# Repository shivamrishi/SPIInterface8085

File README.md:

# SPIInterface8085

Protocols like SPI and I2C are not supported by 8085 processors without any external peripherals and IC's. 
Therefore, bit-banging is used to communicate with 8085 based system. Addressable latches are used for this purpose. the details can be found in compass.sch.

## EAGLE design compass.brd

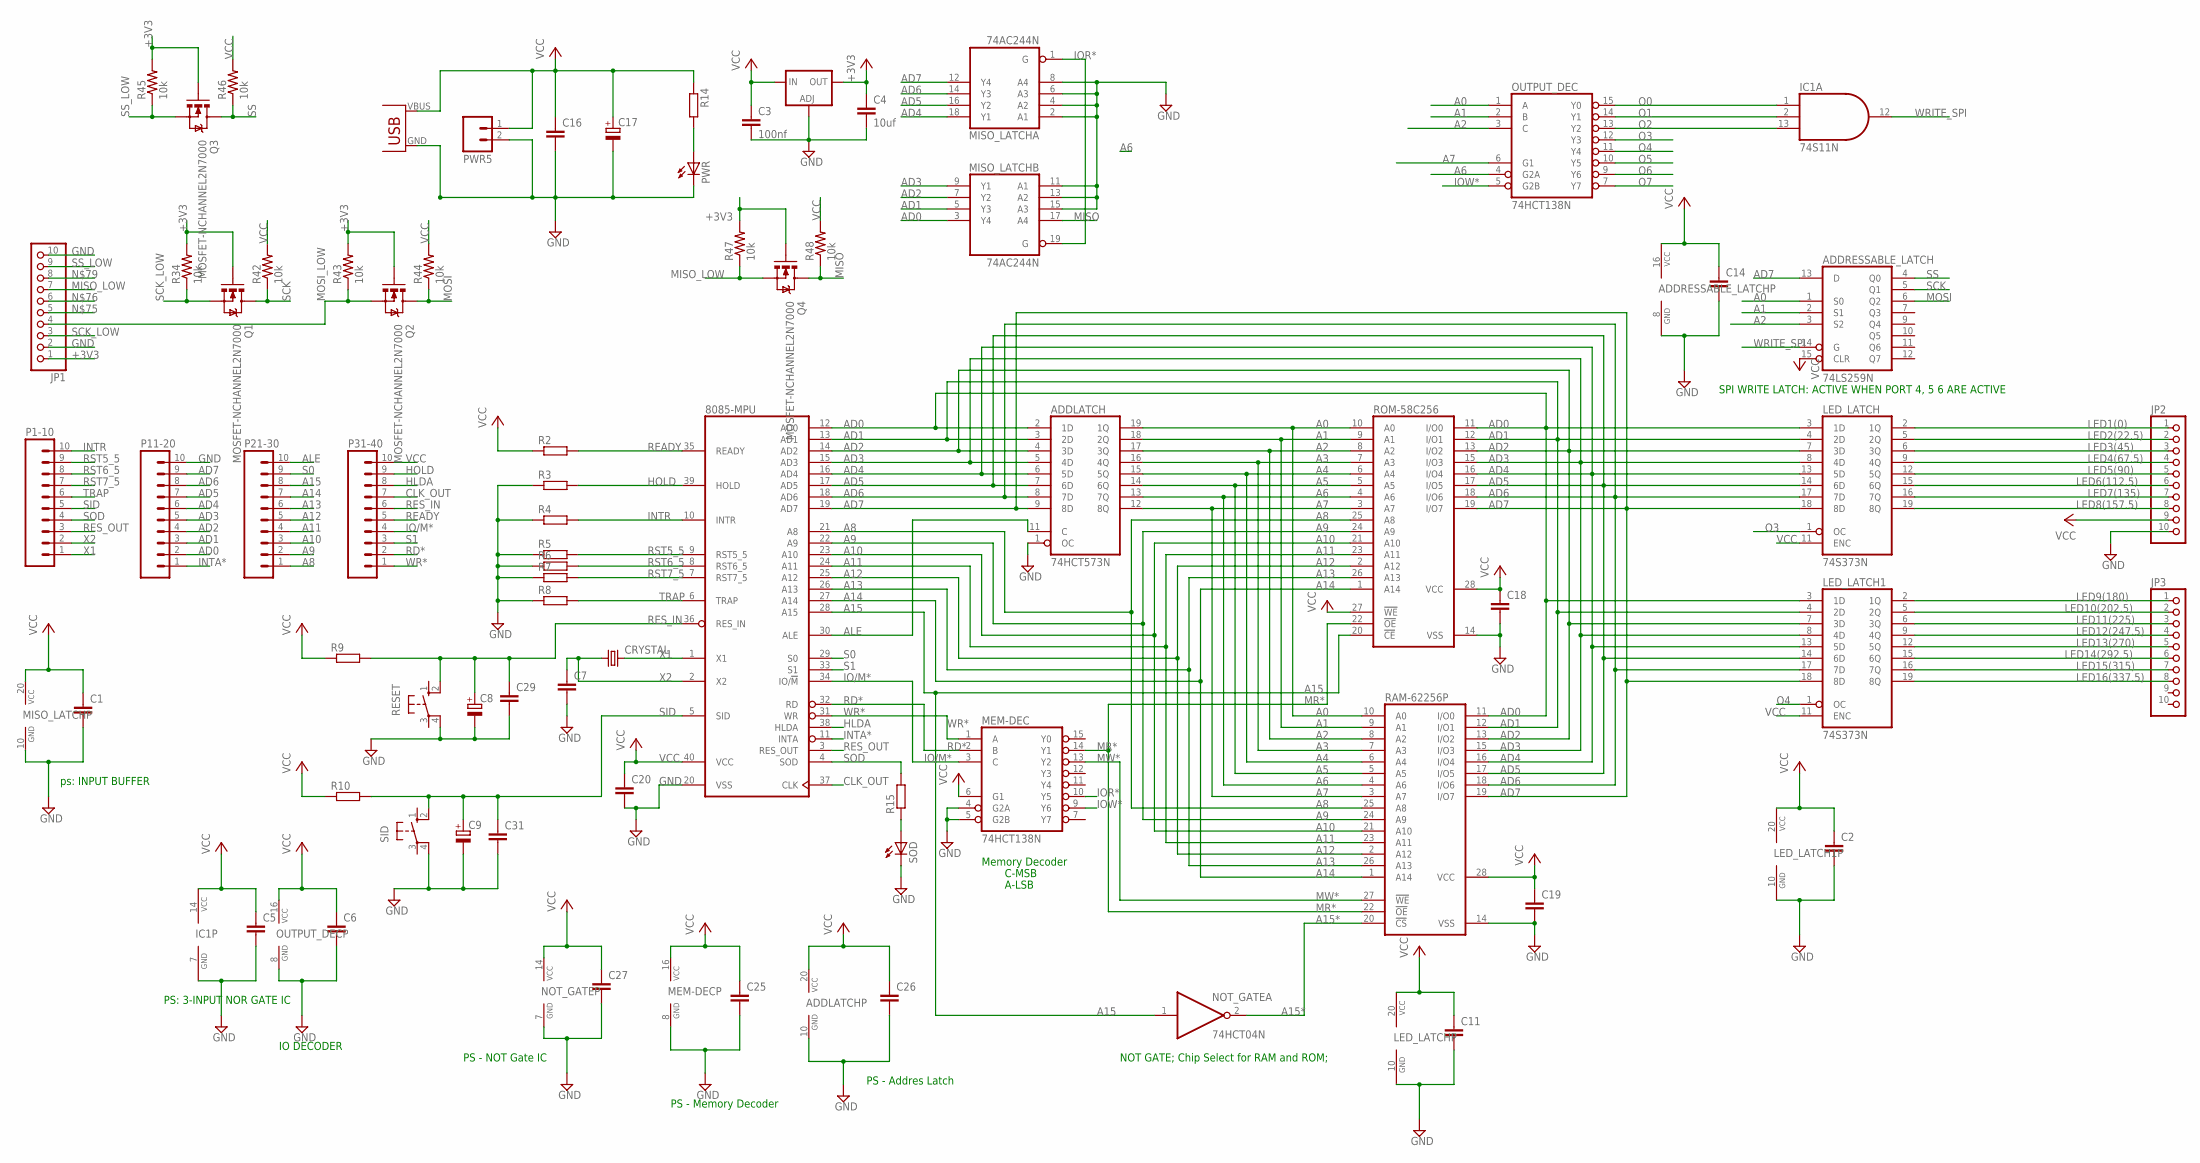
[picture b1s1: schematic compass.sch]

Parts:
8085-MPU: 8085; DIL40
ADDLATCH: 74HCT573N; DIL20
ADDRESSABLE_LATCH: 74LS259N; DIL16
C1, C2, C5, C6, C7, C11, C14, C16, C18, C19, C20, C25, C26, C27, C29, C31: C-EU025-025X050; C025-025X050
C3: 100nf; C025-025X050
C4: 10uf; C025-025X050
C8, C9, C17: CPOL-EUE2.5-6; E2,5-6
CRYSTAL: CRYSTALHC49US; HC49US
IC1: 74S11N; DIL14
IC10: LD117AS33TR; SOT223
JP1, JP2, JP3: PINHD-1X10; 1X10
LED_LATCH, LED_LATCH1: 74S373N; DIL20
MEM-DEC: 74HCT138N; DIL16
MISO_LATCH: 74AC244N; DIL20
NOT_GATE: 74HCT04N; DIL14
OUTPUT_DEC: 74HCT138N; DIL16
P1-10, P11-20, P21-30, P31-40: M10; 10P
PWR: LED5MM
PWR5: M02; 02P
Q1, Q2, Q3, Q4: MOSFET-NCHANNEL2N7000; TO-92
R2, R3, R4, R5, R6, R7, R8, R9, R10, R14, R15: R-EU_0204/7; 0204/7
R34, R42, R43, R44, R45, R46, R47, R48: 10k; 0204/7
RAM-62256P: 62256P; DIL28-6
RESET: 10-XX; B3F-10XX
ROM-58C256: 58C256P; DIL28-6
SID: 10-XX; B3F-10XX
SOD: LED5MM
USB: USB(POWER)

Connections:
+3V3: C4.1, IC10.4 (OUT), JP1.1, Q1.2 (G), Q2.2 (G), Q3.2 (G), Q4.2 (G), R34.2, R43.2, R45.2, R47.2
A0: ADDLATCH.19 (1Q), ADDRESSABLE_LATCH.1 (S0), OUTPUT_DEC.1 (A), RAM-62256P.10 (A0), ROM-58C256.10 (A0)
A1: ADDLATCH.18 (2Q), ADDRESSABLE_LATCH.2 (S1), OUTPUT_DEC.2 (B), RAM-62256P.9 (A1), ROM-58C256.9 (A1)
A2: ADDLATCH.17 (3Q), ADDRESSABLE_LATCH.3 (S2), OUTPUT_DEC.3 (C), RAM-62256P.8 (A2), ROM-58C256.8 (A2)
A3: ADDLATCH.16 (4Q), RAM-62256P.7 (A3), ROM-58C256.7 (A3)
A4: ADDLATCH.15 (5Q), RAM-62256P.6 (A4), ROM-58C256.6 (A4)
A5: ADDLATCH.14 (6Q), RAM-62256P.5 (A5), ROM-58C256.5 (A5)
A6: ADDLATCH.13 (7Q), OUTPUT_DEC.4 (G2A), RAM-62256P.4 (A6), ROM-58C256.4 (A6)
A7: ADDLATCH.12 (8Q), OUTPUT_DEC.6 (G1), RAM-62256P.3 (A7), ROM-58C256.3 (A7)
A8: 8085-MPU.21 (A8), P21-30.1, RAM-62256P.25 (A8), ROM-58C256.25 (A8)
A9: 8085-MPU.22 (A9), P21-30.2, RAM-62256P.24 (A9), ROM-58C256.24 (A9)
A10: 8085-MPU.23 (A10), P21-30.3, RAM-62256P.21 (A10), ROM-58C256.21 (A10)
A11: 8085-MPU.24 (A11), P21-30.4, RAM-62256P.23 (A11), ROM-58C256.23 (A11)
A12: 8085-MPU.25 (A12), P21-30.5, RAM-62256P.2 (A12), ROM-58C256.2 (A12)
A13: 8085-MPU.26 (A13), P21-30.6, RAM-62256P.26 (A13), ROM-58C256.26 (A13)
A14: 8085-MPU.27 (A14), P21-30.7, RAM-62256P.1 (A14), ROM-58C256.1 (A14)
A15: 8085-MPU.28 (A15), NOT_GATE.1 (I), P21-30.8, ROM-58C256.20 (!CE)
A15*: NOT_GATE.2 (O), RAM-62256P.20 (!CS)
AD0: 8085-MPU.12 (AD0), ADDLATCH.2 (1D), LED_LATCH.3 (1D), LED_LATCH1.3 (1D), MISO_LATCH.3 (Y4), P11-20.2, RAM-62256P.11 (I/O0), ROM-58C256.11 (I/O0)
AD1: 8085-MPU.13 (AD1), ADDLATCH.3 (2D), LED_LATCH.4 (2D), LED_LATCH1.4 (2D), MISO_LATCH.5 (Y3), P11-20.3, RAM-62256P.12 (I/O1), ROM-58C256.12 (I/O1)
AD2: 8085-MPU.14 (AD2), ADDLATCH.4 (3D), LED_LATCH.7 (3D), LED_LATCH1.7 (3D), MISO_LATCH.7 (Y2), P11-20.4, RAM-62256P.13 (I/O2), ROM-58C256.13 (I/O2)
AD3: 8085-MPU.15 (AD3), ADDLATCH.5 (4D), LED_LATCH.8 (4D), LED_LATCH1.8 (4D), MISO_LATCH.9 (Y1), P11-20.5, RAM-62256P.15 (I/O3), ROM-58C256.15 (I/O3)
AD4: 8085-MPU.16 (AD4), ADDLATCH.6 (5D), LED_LATCH.13 (5D), LED_LATCH1.13 (5D), MISO_LATCH.18 (Y1), P11-20.6, RAM-62256P.16 (I/O4), ROM-58C256.16 (I/O4)
AD5: 8085-MPU.17 (AD5), ADDLATCH.7 (6D), LED_LATCH.14 (6D), LED_LATCH1.14 (6D), MISO_LATCH.16 (Y2), P11-20.7, RAM-62256P.17 (I/O5), ROM-58C256.17 (I/O5)
AD6: 8085-MPU.18 (AD6), ADDLATCH.8 (7D), LED_LATCH.17 (7D), LED_LATCH1.17 (7D), MISO_LATCH.14 (Y3), P11-20.8, RAM-62256P.18 (I/O6), ROM-58C256.18 (I/O6)
AD7: 8085-MPU.19 (AD7), ADDLATCH.9 (8D), ADDRESSABLE_LATCH.13 (D), LED_LATCH.18 (8D), LED_LATCH1.18 (8D), MISO_LATCH.12 (Y4), P11-20.9, RAM-62256P.19 (I/O7), ROM-58C256.19 (I/O7)
ALE: 8085-MPU.30 (ALE), ADDLATCH.11 (C), P21-30.10
CLK_OUT: 8085-MPU.37 (CLK), P31-40.7
GND: 8085-MPU.20 (VSS), ADDLATCH.1 (OC), ADDLATCH.10 (GND), ADDRESSABLE_LATCH.8 (GND), C1.2, C2.2, C3.2, C4.2, C5.2, C6.2, C7.2, C8.-, C9.-, C11.2, C14.2, C16.2, C17.-, C18.2, C19.2, C20.2, C25.2, C26.2, C27.2, C29.2, C31.2, IC1.7 (GND), IC10.1 (ADJ), JP1.2, JP1.10, JP2.10, LED_LATCH.10 (GND), LED_LATCH1.10 (GND), MEM-DEC.4 (G2A), MEM-DEC.5 (G2B), MEM-DEC.8 (GND), MISO_LATCH.2 (A1), MISO_LATCH.4 (A2), MISO_LATCH.6 (A3), MISO_LATCH.8 (A4), MISO_LATCH.10 (GND), MISO_LATCH.11 (A1), MISO_LATCH.13 (A2), MISO_LATCH.15 (A3), NOT_GATE.7 (GND), OUTPUT_DEC.8 (GND), P11-20.10, PWR.K (C), PWR5.2, R3.1, R4.1, R5.1, R6.1, R7.1, R8.1, RAM-62256P.14 (VSS), RESET.4 (P1), ROM-58C256.14 (VSS), SID.4 (P1), SOD.K (C), USB.GND
HLDA: 8085-MPU.38 (HLDA), P31-40.8
HOLD: 8085-MPU.39 (HOLD), P31-40.9, R3.2
INTA*: 8085-MPU.11 (INTA), P11-20.1
INTR: 8085-MPU.10 (INTR), P1-10.10, R4.2
IO/M*: 8085-MPU.34 (IO/!M), MEM-DEC.3 (C), P31-40.4
IOR*: MEM-DEC.10 (Y5), MISO_LATCH.1 (G), MISO_LATCH.19 (G)
IOW*: MEM-DEC.9 (Y6), OUTPUT_DEC.5 (G2B)
LED1(0): JP2.1, LED_LATCH.2 (1Q)
LED2(22.5): JP2.2, LED_LATCH.5 (2Q)
LED3(45): JP2.3, LED_LATCH.6 (3Q)
LED4(67.5): JP2.4, LED_LATCH.9 (4Q)
LED5(90): JP2.5, LED_LATCH.12 (5Q)
LED6(112.5): JP2.6, LED_LATCH.15 (6Q)
LED7(135): JP2.7, LED_LATCH.16 (7Q)
LED8(157.5): JP2.8, LED_LATCH.19 (8Q)
LED9(180): JP3.1, LED_LATCH1.2 (1Q)
LED10(202.5): JP3.2, LED_LATCH1.5 (2Q)
LED11(225): JP3.3, LED_LATCH1.6 (3Q)
LED12(247.5): JP3.4, LED_LATCH1.9 (4Q)
LED13(270): JP3.5, LED_LATCH1.12 (5Q)
LED14(292.5): JP3.6, LED_LATCH1.15 (6Q)
LED15(315): JP3.7, LED_LATCH1.16 (7Q)
LED16(337.5): JP3.8, LED_LATCH1.19 (8Q)
MISO: MISO_LATCH.17 (A4), Q4.3 (D), R48.1
MISO_LOW: JP1.7, Q4.1 (S), R47.1
MOSI: ADDRESSABLE_LATCH.6 (Q2), Q2.3 (D), R44.1
MOSI_LOW: JP1.4, Q2.1 (S), R43.1
MR*: MEM-DEC.14 (Y1), RAM-62256P.22 (!OE), ROM-58C256.22 (!OE)
MW*: MEM-DEC.13 (Y2), RAM-62256P.27 (!WE)
unnamed: R15.1, SOD.A
unnamed: PWR.A, R14.2
O0: IC1.1 (I0), OUTPUT_DEC.15 (Y0)
O1: IC1.2 (I1), OUTPUT_DEC.14 (Y1)
O2: IC1.13 (I2), OUTPUT_DEC.13 (Y2)
O3: LED_LATCH.1 (OC), OUTPUT_DEC.12 (Y3)
O4: LED_LATCH1.1 (OC), OUTPUT_DEC.11 (Y4)
O5: OUTPUT_DEC.10 (Y5)
O6: OUTPUT_DEC.9 (Y6)
O7: OUTPUT_DEC.7 (Y7)
RD*: 8085-MPU.32 (RD), MEM-DEC.2 (B), P31-40.2
READY: 8085-MPU.35 (READY), P31-40.5, R2.2
RES_IN: 8085-MPU.36 (RES_IN), C8.+, C29.1, P31-40.6, R9.2, RESET.2 (S1)
RES_OUT: 8085-MPU.3 (RES_OUT), P1-10.3
RST5_5: 8085-MPU.9 (RST5_5), P1-10.9, R5.2
RST6_5: 8085-MPU.8 (RST6_5), P1-10.8, R6.2
RST7_5: 8085-MPU.7 (RST7_5), P1-10.7, R7.2
S0: 8085-MPU.29 (S0), P21-30.9
S1: 8085-MPU.33 (S1), P31-40.3
SCK: ADDRESSABLE_LATCH.5 (Q1), Q1.3 (D), R42.1
SCK_LOW: JP1.3, Q1.1 (S), R34.1
SID: 8085-MPU.5 (SID), C9.+, C31.1, P1-10.5, R10.2, SID.2 (S1)
SOD: 8085-MPU.4 (SOD), P1-10.4, R15.2
SS: ADDRESSABLE_LATCH.4 (Q0), Q3.3 (D), R46.1
SS_LOW: JP1.9, Q3.1 (S), R45.1
TRAP: 8085-MPU.6 (TRAP), P1-10.6, R8.2
VCC: 8085-MPU.40 (VCC), ADDLATCH.20 (VCC), ADDRESSABLE_LATCH.15 (CLR), ADDRESSABLE_LATCH.16 (VCC), C1.1, C2.1, C3.1, C5.1, C6.1, C11.1, C14.1, C16.1, C17.+, C18.1, C19.1, C20.1, C25.1, C26.1, C27.1, IC1.14 (VCC), IC10.3 (IN), JP2.9, LED_LATCH.11 (ENC), LED_LATCH.20 (VCC), LED_LATCH1.11 (ENC), LED_LATCH1.20 (VCC), MEM-DEC.6 (G1), MEM-DEC.16 (VCC), MISO_LATCH.20 (VCC), NOT_GATE.14 (VCC), OUTPUT_DEC.16 (VCC), P31-40.10, PWR5.1, R2.1, R9.1, R10.1, R14.1, R42.2, R44.2, R46.2, R48.2, RAM-62256P.28 (VCC), ROM-58C256.27 (!WE), ROM-58C256.28 (VCC), USB.VBUS (VCC)
WR*: 8085-MPU.31 (WR), MEM-DEC.1 (A), P31-40.1
WRITE_SPI: ADDRESSABLE_LATCH.14 (G), IC1.12 (O)
X1: 8085-MPU.1 (X1), CRYSTAL.2, P1-10.1
X2: 8085-MPU.2 (X2), C7.1, CRYSTAL.1, P1-10.2

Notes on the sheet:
PS - NOT Gate IC
PS - Memory Decoder
PS - Addres Latch
Memory Decoder
C-MSB
A-LSB
NOT GATE; Chip Select for RAM and ROM;
SPI WRITE LATCH: ACTIVE WHEN PORT 4, 5 6 ARE ACTIVE
ps: INPUT BUFFER
PS: 3-INPUT NOR GATE IC
IO DECODER

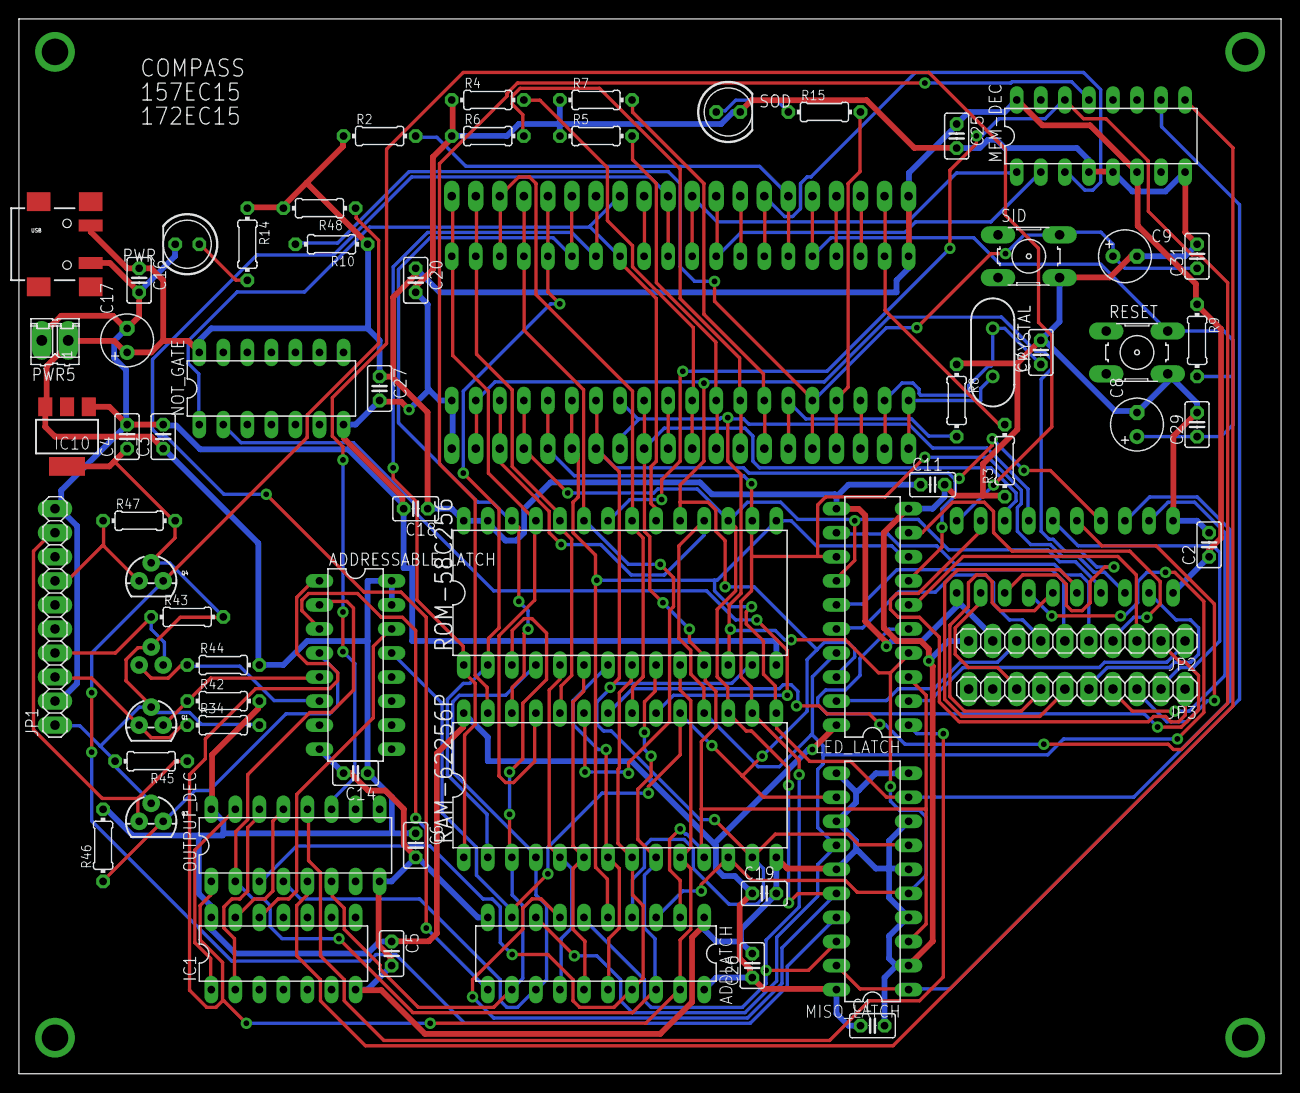
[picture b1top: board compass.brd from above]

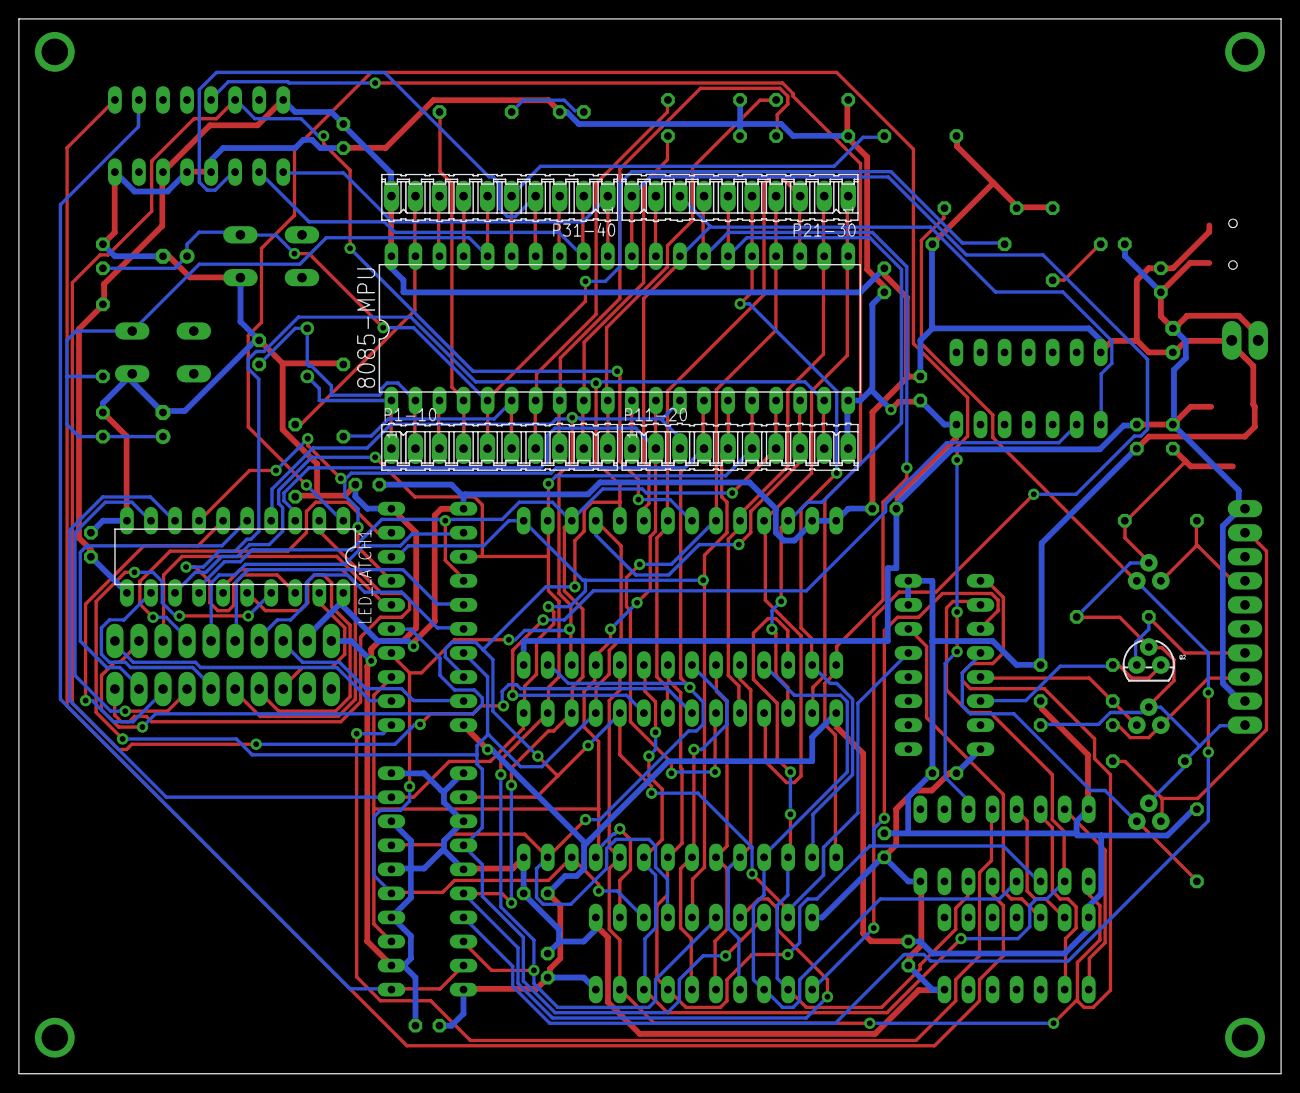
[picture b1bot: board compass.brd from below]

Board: 2 copper layers, 133.3 x 111.4 mm, 71 parts (7 on the bottom side), 86 nets.

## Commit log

2018-04-16 spi test code working
2018-04-17 successful magnetometer intialization
2018-04-17 complete code added
2018-04-17 added send_mag_data subroutine

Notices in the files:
parts and their libraries:
SparkFun-DiscreteSemi: Licensing: Creative Commons ShareAlike 4.0 International - https://creativecommons.org/licenses/by-sa/4.0
